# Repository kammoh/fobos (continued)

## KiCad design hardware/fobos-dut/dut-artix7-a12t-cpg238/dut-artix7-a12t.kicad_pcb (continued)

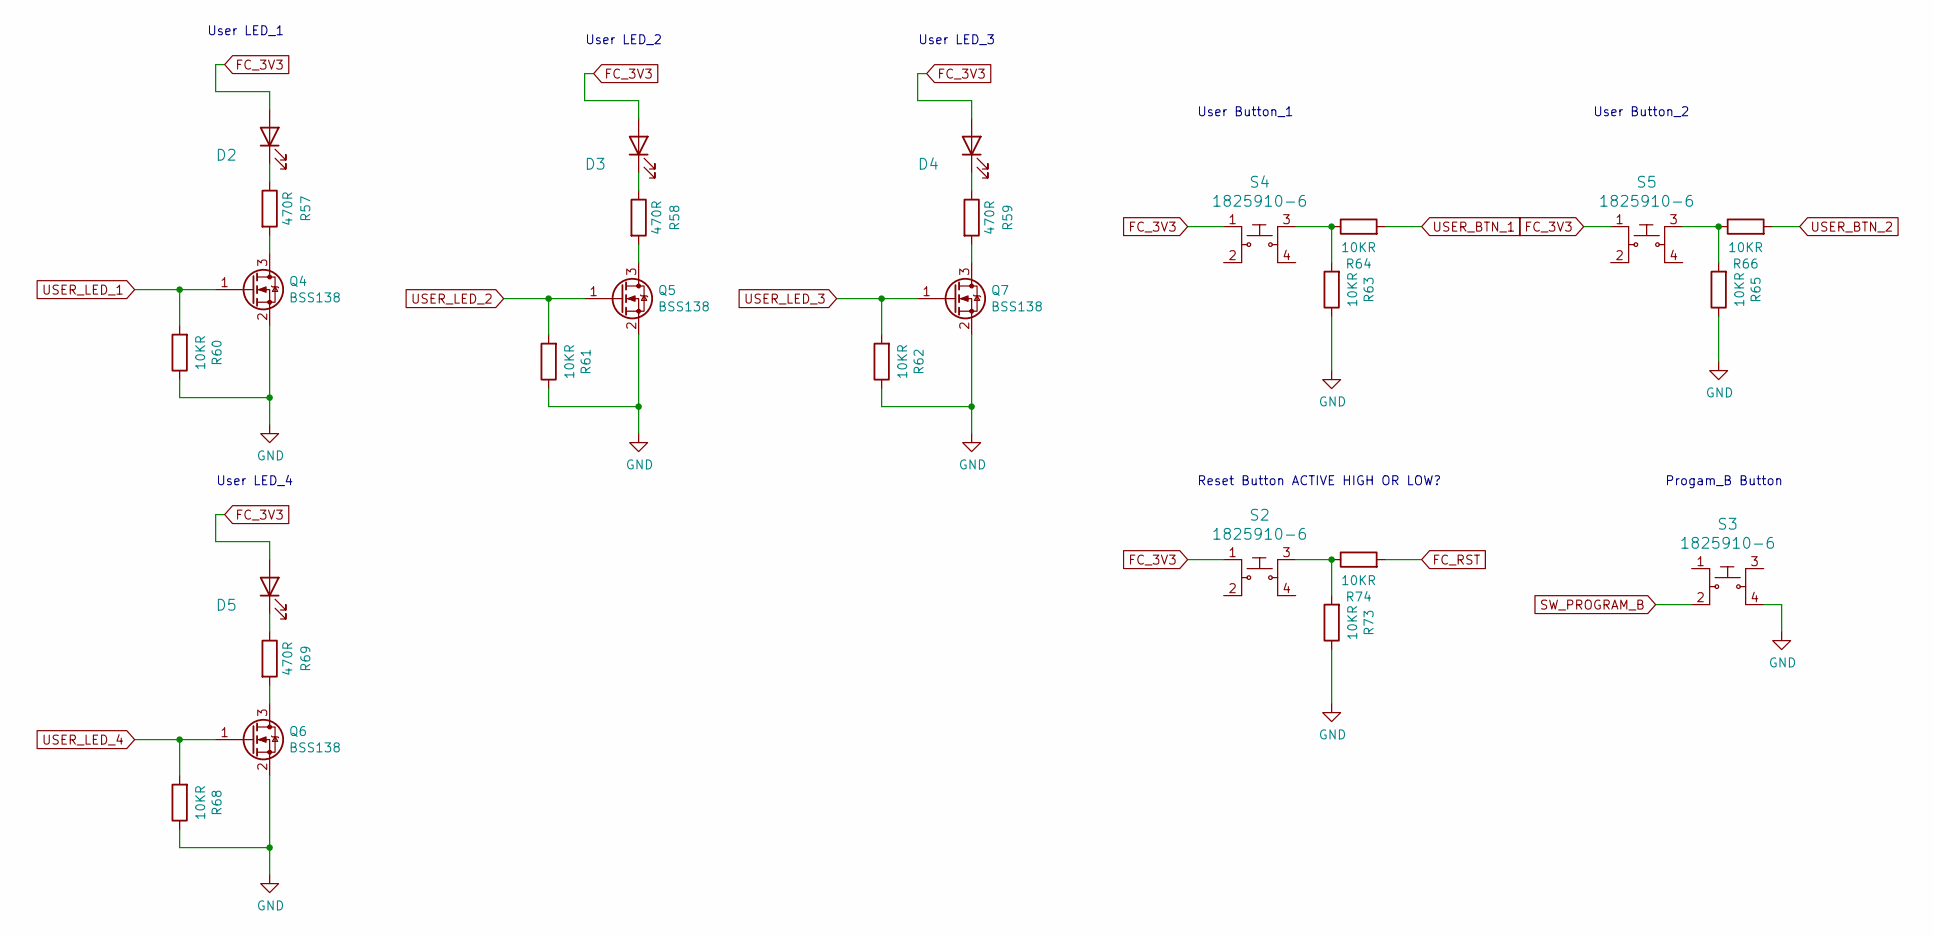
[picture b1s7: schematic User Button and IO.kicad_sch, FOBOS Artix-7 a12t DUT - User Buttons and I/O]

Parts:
D2, D3, D4, D5: LG_L29K-G2J1-24-Z; LED_0603_1608Metric; MPN LG L29K-G2J1-24-Z; Digi-Key_PN 475-2709-1-ND
Q4, Q5, Q6, Q7: BSS138; SOT-23; MPN BSS138
R57, R58, R59, R69: 470R; R_0603_1608Metric; MPN ERJ-U03J471V
R60, R61, R62, R63, R64, R65, R66, R68, R73, R74: 10KR; R_0603_1608Metric; MPN ERJ-3EKF1002V
S2, S3, S4, S5: 1825910-6; Switch_Tactile_THT_6x6mm; MPN 1825910-6; Digi-Key_PN 450-1650-ND

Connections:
FC_RST: R74.2; also elsewhere on the board
GND: Q4.2 (S), Q5.2 (S), Q6.2 (S), Q7.2 (S), R60.1, R61.1, R62.1, R63.1, R65.1, R68.1, R73.1, S3.4; also elsewhere on the board
unnamed: D2.1 (K), R57.1
unnamed: D3.1 (K), R58.1
unnamed: D4.1 (K), R59.1
unnamed: D5.1 (K), R69.1
unnamed: Q4.3 (D), R57.2
unnamed: Q5.3 (D), R58.2
unnamed: Q6.3 (D), R69.2
unnamed: Q7.3 (D), R59.2
unnamed: R63.2, R64.1, S4.3
unnamed: R65.2, R66.1, S5.3
unnamed: R73.2, R74.1, S2.3
SW_PROGRAM_B: S3.2; also elsewhere on the board
USER_BTN_1: R64.2; also elsewhere on the board
USER_BTN_2: R66.2; also elsewhere on the board
USER_LED_1: Q4.1 (G), R60.2; also elsewhere on the board
USER_LED_2: Q5.1 (G), R61.2; also elsewhere on the board
USER_LED_3: Q7.1 (G), R62.2; also elsewhere on the board
USER_LED_4: Q6.1 (G), R68.2; also elsewhere on the board

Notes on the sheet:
User LED_2
User LED_3
User LED_1
Reset Button ACTIVE HIGH OR LOW?
User Button_1
User LED_4
Progam_B Button
User Button_2

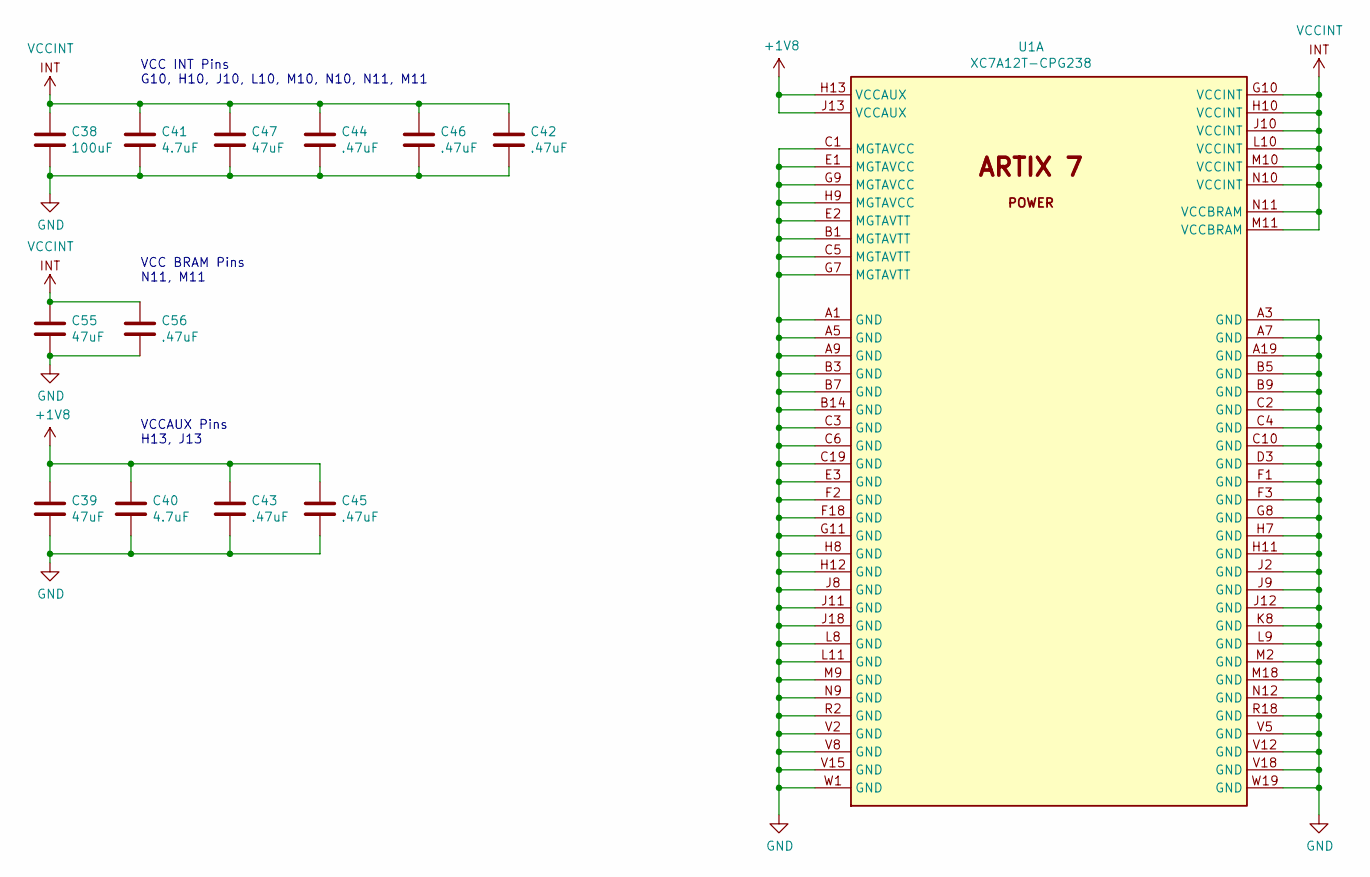
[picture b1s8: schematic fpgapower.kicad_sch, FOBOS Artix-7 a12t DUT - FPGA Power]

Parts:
C38: 100uF; C_1210_3225Metric_Pad1.33x2.70mm_HandSolder; MPN JMK325ABJ107MM-P
C39, C47, C55: 47uF; C_0603_1608Metric_Pad1.08x0.95mm_HandSolder; MPN 06036D476MAT2A
C40, C41: 4.7uF; C_0402_1005Metric_Pad0.74x0.62mm_HandSolder; MPN GRM155R60J475ME87J
C42, C43, C44, C45, C46, C56: .47uF; C_0402_1005Metric_Pad0.74x0.62mm_HandSolder; MPN C0402C474K9PACTU
U1: XC7A12T-CPG238; Xilinx_CPG238

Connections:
GND: C38.2, C39.2, C40.2, C41.2, C42.2, C43.2, C44.2, C45.2, C46.2, C47.2, C55.2, C56.2, U1.A1 (GND), U1.A3 (GND), U1.A5 (GND), U1.A7 (GND), U1.A9 (GND), U1.A19 (GND), U1.B1 (MGTAVTT), U1.B3 (GND), U1.B5 (GND), U1.B7 (GND), U1.B9 (GND), U1.B14 (GND), U1.C1 (MGTAVCC), U1.C2 (GND), U1.C3 (GND), U1.C4 (GND), U1.C5 (MGTAVTT), U1.C6 (GND), U1.C10 (GND), U1.C19 (GND), U1.D3 (GND), U1.E1 (MGTAVCC), U1.E2 (MGTAVTT), U1.E3 (GND), U1.F1 (GND), U1.F2 (GND), U1.F3 (GND), U1.F18 (GND), U1.G7 (MGTAVTT), U1.G8 (GND), U1.G9 (MGTAVCC), U1.G11 (GND), U1.H7 (GND), U1.H8 (GND), U1.H9 (MGTAVCC), U1.H11 (GND), U1.H12 (GND), U1.J2 (GND), U1.J8 (GND), U1.J9 (GND), U1.J11 (GND), U1.J12 (GND), U1.J18 (GND), U1.K8 (GND), U1.L8 (GND), U1.L9 (GND), U1.L11 (GND), U1.M2 (GND), U1.M9 (GND), U1.M18 (GND), U1.N9 (GND), U1.N12 (GND), U1.R2 (GND), U1.R18 (GND), U1.V2 (GND), U1.V5 (GND), U1.V8 (GND), U1.V12 (GND), U1.V15 (GND), U1.V18 (GND), U1.W1 (GND), U1.W19 (GND); also elsewhere on the board
VCCINT: C38.1, C41.1, C42.1, C44.1, C46.1, C47.1, C55.1, C56.1, U1.G10 (VCCINT), U1.H10 (VCCINT), U1.J10 (VCCINT), U1.L10 (VCCINT), U1.M10 (VCCINT), U1.M11 (VCCBRAM), U1.N10 (VCCINT), U1.N11 (VCCBRAM); also elsewhere on the board

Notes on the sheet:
VCCAUX Pins H13, J13
VCC BRAM Pins N11, M11
VCC INT Pins G10, H10, J10, L10, M10, N10, N11, M11

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
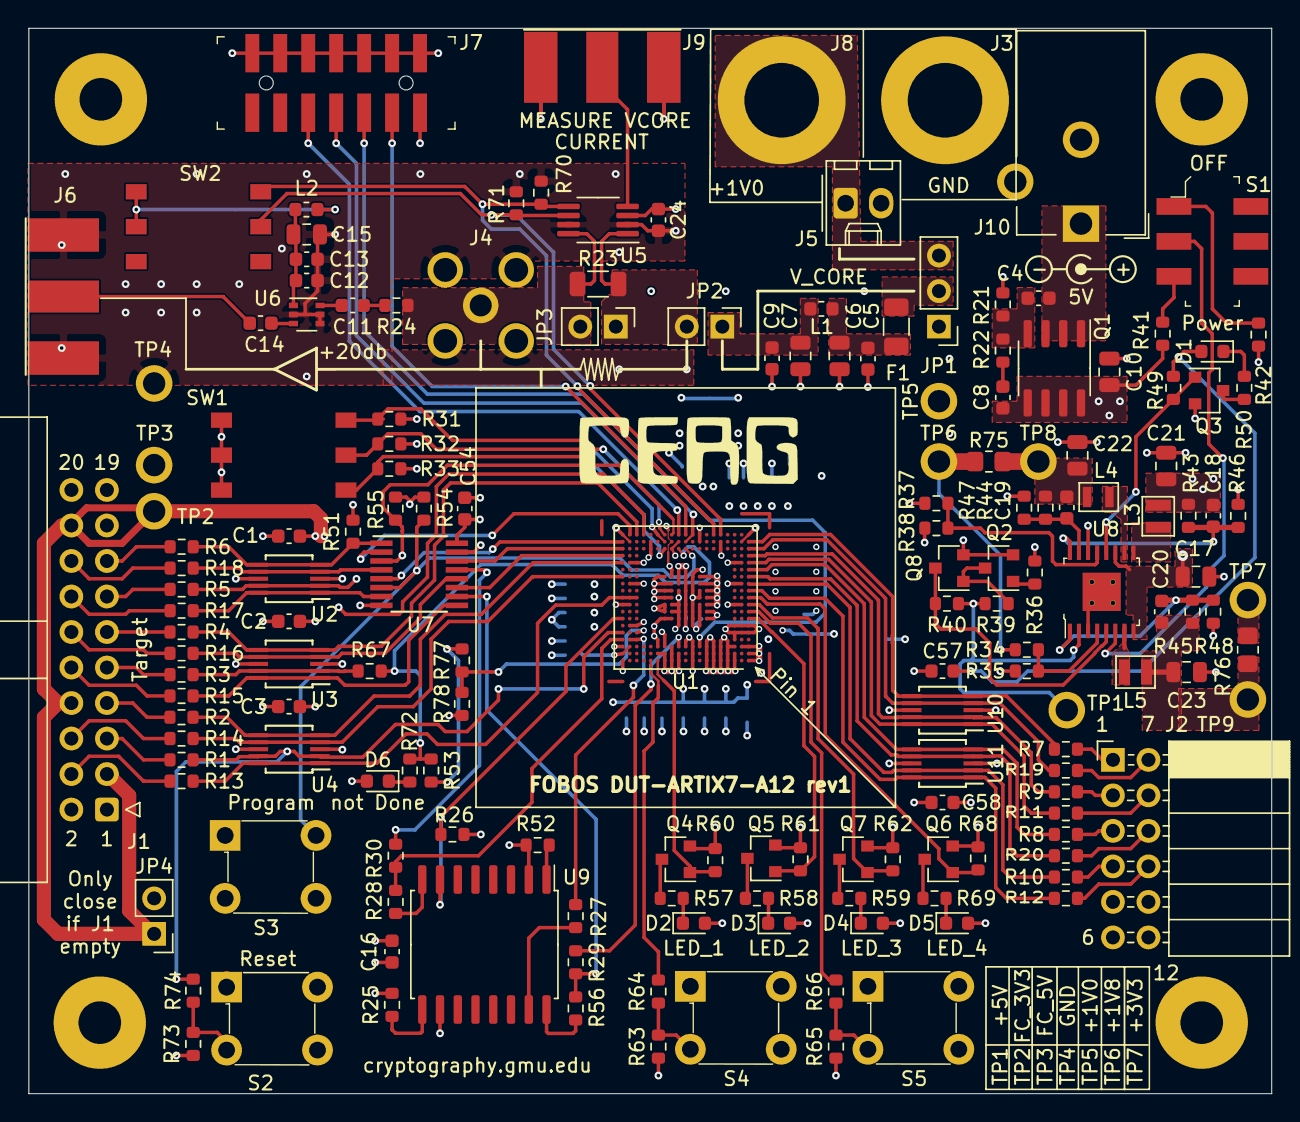
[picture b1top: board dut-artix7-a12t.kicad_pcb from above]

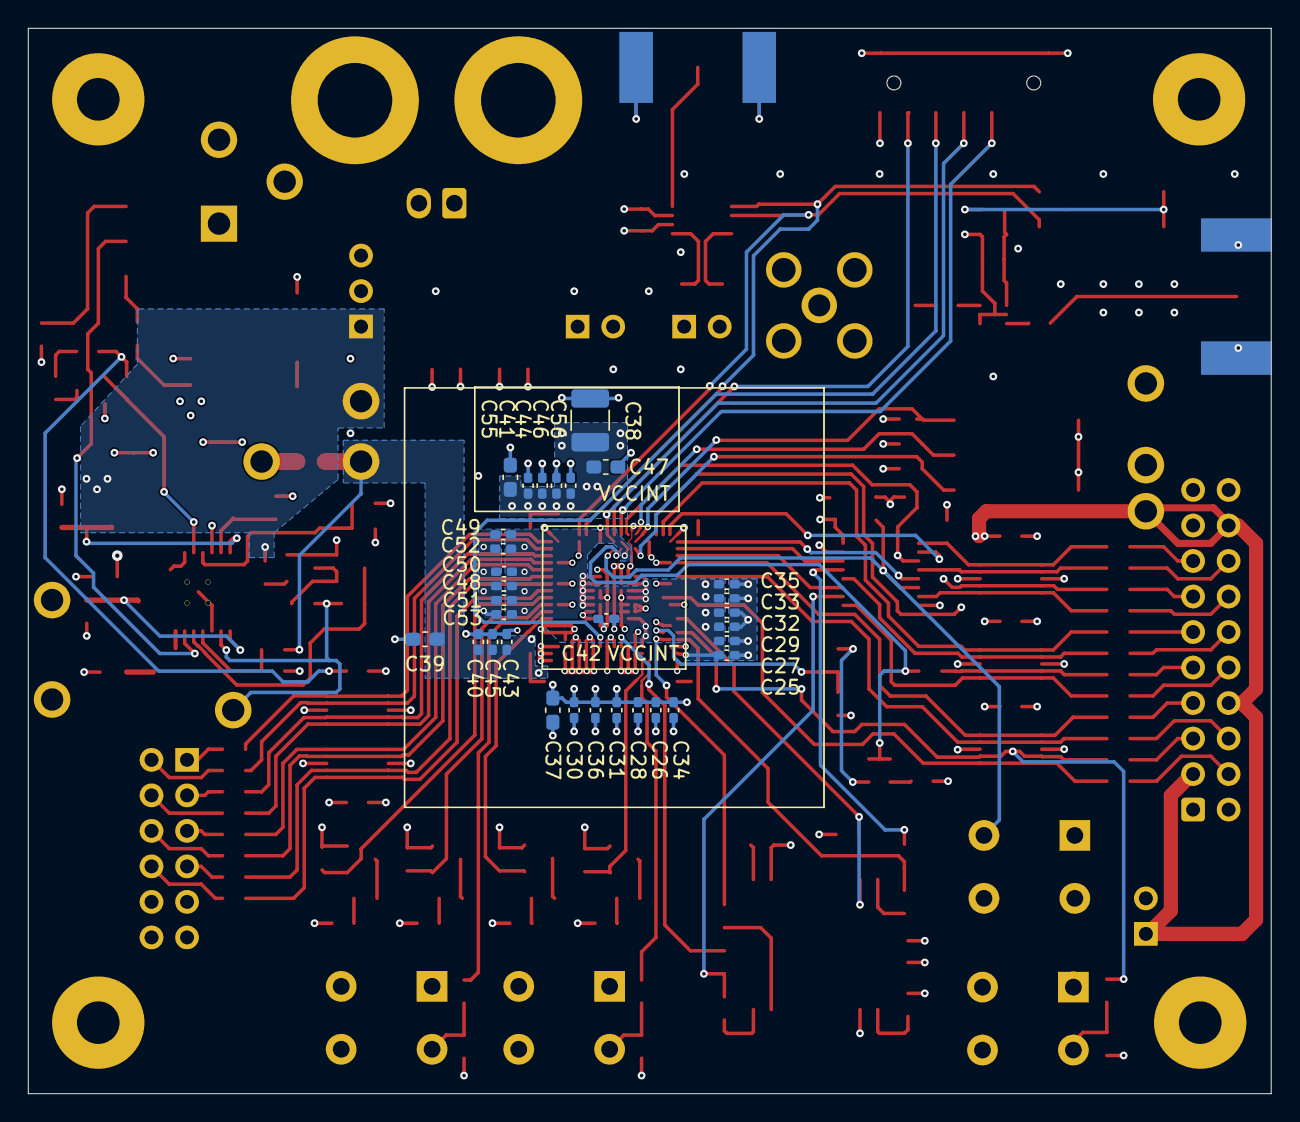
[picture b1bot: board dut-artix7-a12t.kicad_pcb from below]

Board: 4 copper layers, 88.9 x 76.2 mm, 201 parts (31 on the bottom side), 126 nets.

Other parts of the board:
TP6, TP7, TP8, TP9: 5281

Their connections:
/Power/pre3V3: TP9.1; also elsewhere on the board

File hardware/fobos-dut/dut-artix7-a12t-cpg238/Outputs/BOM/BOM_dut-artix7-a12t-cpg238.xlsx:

Artix-7 DUT
Ref# | Qty. | Value | Size | Mouser # | Mfr. # | Manufacturer | Description
R29 R30 R37 R67 | 4 | 0R | 0603 | 603-RC0603JR-070RL | RC0603JR-070RL | Yageo | Thick Film Resistors - SMD 0 Ohms 100 mW 0603 5%
R23 | 1 | 0R1 | 1206 | 71-WSL1206R1000DEA | WSL1206R1000DEA | Vishay | Current Sense Resistors - SMD 1/4watt .1ohms .5%
R24 | 1 | 49R9 | 0603
R75 R76 | 2 | 0R1 | 0805
R22 | 1 | 100R | 0603 | 603-RC0603FR-13100RL | RC0603FR-13100RL | Yageo | Thick Film Resistors - SMD 100 OHM 1%
R36 R77 R78 | 3 | 1k | 0603 | 603-RC0603FR-071KL | RC0603FR-071KL | Yageo | Thick Film Resistors - SMD 1K OHM 1%
R35 R42 R43 R44 R45 R51 R60 R61 R62 R63 R64 R65 R66 R68 R70 R71 R73 R74 | 18 | 10k | 0603 | 603-RC0603FR-0710KL | RC0603FR-0710KL | Yageo | Thick Film Resistors - SMD 10K OHM 1%
R38 R39 R40 R49 | 4 | 100k | 0603 | 652-CR0603-FX-103ELF | CR0603-FX-1003ELF | Bourns | Thick Film Resistors - SMD 100K 1% 1/10 WATT
R21 | 1 | 1M | 0603 | 652-CR0603FX-1004ELF | CR0603-FX-1004ELF | Bourns | Thick Film Resistors - SMD 1M 1% 1/10W
R46 R47 | 2 | 120k | 0603 | 603-RC0603FR-13120KL | RC0603FR-13120KL | Yageo | Thick Film Resistors - SMD 120 kOhms 100-200 mW 0603 1%
R7 R8 R9 R10 R11 R12 R19 R20 R53 R72 | 10 | 200R | 0603 | 603-RC0603FR-07200RL | RC0603FR-07200RL | Yageo | Thick Film Resistors - SMD 200 OHM 1%
R1 R2 R3 R4 R5 R6 R13 R14 R15 R16 R17 R18 | 12 | 22R | 0603 | 603-RC0603FR-0722RL | RC0603FR-0722RL | Yageo | Thick Film Resistors - SMD 22 OHM 1%
R27 R28 R56 | 3 | 33R, 0.5% | 0603 | 667-ERA-3AHD330V | ERA-3AHD330V | Panasonic | Thin Film Resistors - SMD 0603 33ohms 50ppm 0.5% AEC-Q200
R34 | 1 | 3k48 | 0603 | 603-RC0603FR-073K48L | RC0603FR-073K48L | Yageo | Thick Film Resistors - SMD 3.48 kOhms 100mW 0603 1%
R57 R58 R59 R69 | 4 | 470R | 0603 | 603-RC0603FR-10470RL | RC0603FR-10470RL | Yageo | Thick Film Resistors - SMD 470 OHM 1%
R25 R26 R31 R32 R33 R41 R52 R54 R55 | 9 | 4k7 | 0603 | 603-RC0603FR-134K7L | RC0603FR-134K7L | Yageo | Thick Film Resistors - SMD 4.7 kOhms 100-200mW 0603 1%
R48 | 1 | 57k6 | 0603 | 652-CR0603FX-5762ELF | CR0603-FX-5762ELF | Bourns | Thick Film Resistors - SMD 57.6K ohm 1%
R50 | 1 | 800R | 0603 | 603-RC0603FR-07806RL | RC0603FR-07806RL | Yageo | Thick Film Resistors - SMD 806 Ohms 100 mW 0603 1%
C8 | 1 | 10nF | 0603 | 603-CS0603KRX79BB103 | CS0603KRX7R9BB103 | Yageo | Multilayer Ceramic Capacitors MLCC - SMD/SMT 10 nF 50 V 10% Ceramic Capacitors
C1 C2 C3 C4 C5 C9 C11 C13 C14 C16 C24 C54 C57 C58 | 14 | 100nF | 0603 | 77-VJ0603Y104JXQPBC | VJ0603Y104JXQPW1BC | Vishay / Vitramon | Multilayer Ceramic Capacitors MLCC - SMD/SMT 0603 0.1uF 10volts X7R 5%
C6 C10 C22 C23 | 4 | 10uF | 0805 | 81-GRM21BC81C106MA3L | GRM21BC81C106MA73L | Murata Electronics | Multilayer Ceramic Capacitors MLCC - SMD/SMT 0805 10uF 16volts X6S 20%
C18 C19 C20 | 3 | 20pF | 0603 | 80-C0603C200K8HACTU | C0603C200K8HACTU | KEMET | Multilayer Ceramic Capacitors MLCC - SMD/SMT 10V 20pF X8R 0603 10%
C15 | 1 | 2u2F | 0805
C17 C21 | 2 | 22uF | 0805 | 187-CL21A226KQCLRNC | CL21A226KQCLRNC | Samsung | Multilayer Ceramic Capacitors MLCC - SMD/SMT 22uF+/-10% 6.3V X5R 2012
C12 | 1 | 4n7F | 0603 | 710-885012206087 | 885012206087 | Wurth Electronics | Multilayer Ceramic Capacitors MLCC - SMD/SMT WCAP-CSGP 4700pF 0603 10% 50V MLCC
C29 C30 C31 C32 C33 C34 C35 C36 C42 C43 C44 C45 C46 C50 C51 C52 C53 C56 | 18 | 470nF | 0402 | 963-JMK105BJ474KV-F | JMK105BJ474KV-F | Taiyo Yuden | CAP CER 0.47UF 6.3V X5R 0402
C25 C26 C27 C28 C40 C41 C48 C49 | 8 | 4.7uF | 0402 | 81-GRM155R60J475ME8J | GRM155R60J475ME87J | Murata Electronics | CAP CER 4.7UF 6.3V X5R 0402
C37 C39 C47 C55 | 4 | 47uF | 0603 | 81-GRM21BR60J476ME5K | GRM21BR60J476ME15K | Murata Electronics | Multilayer Ceramic Capacitors MLCC - SMD/SMT 0805 47uF 6.3volts
C7 | 1 | 47uF | 0805
C38 | 1 | 100uF | 1210
L1 L2 | 2 | 1k/500mA | 0603 | 963-FBMH1608HM102-T | FBMH1608HM102-T | Taiyo Yuden | Ferrite Beads HI CUR CHIP BD 0603 1000OHMS 25%
L3 | 1 | 1.5uH |  | 652-SRN2012-1R5M | SRN2012-1R5M | Bourns Inc. | FIXED IND 1.5UH 1.8A 108MOHM SMD
L4 | 1 | 3.3uH |  | 963-BRC2012T3R3MD | BRC2012T3R3MD | Taiyo Yuden | FIXED IND 3.3UH 870MA 221MOHM SM
L5 | 1 | 2.2uH |  | 652-SRN2010-2R2M | SRN2010-2R2M | Bourns Inc. | FIXED IND 2.2UH 1.7A 170MOHM SMD
D1 D2 D3 D4 D5 D6 | 6 | green | 0603 | 604-APT1608CGCK | APT1608CGCK | Kingbright | Standard LEDs - SMD Green Water Clear 570nm 40mcd 120deg
Q3 Q4 Q5 Q6 Q7 | 5 | BSS138L | SOT-23-3 | 512-BSS138L | BSS138L | ON Semiconductor | MOSFET 0.20A, 50V N-Channel SOT-23 MOSFET
Q1 | 1 | FDS9435A | SOIC-8 | 512-FDS9435A | FDS9435A | ON Semiconductor/Fairchild | MOSFET SO-8 SGL P-CH -30V
Q2 Q8 | 2 | 3904 | SOT-23-3 | 863-MMBT3904LT1G | MMBT3904LT1G | ON Semiconductor | Bipolar Transistors - BJT NPN GENERAL PURPOSE
U8 | 1 | LTC3569EFE#PBF | 16TSSOP | LTC3569EFE#PBF | LTC3569EFE#PBF | Analog Devices Inc. | Switching Voltage Regulators Programmable 1.2A and 2X600mA, Triple Buck Regulat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
U5 | 1 | INA225 | MSOP-8 | 595-INA225AIDGKT | INA225AIDGKT | Texas Instruments | Current Sense Amplifiers 36V Bidir 0-Drift Ser Crnt-Shunt Mon
U7 | 1 | TS3A5018DBQR | 16SSOP | 595-TS3A5018DBQR | TS3A5018DBQR | Texas Instruments | Analog Switch ICs 10-Ohm Quad SPDT Analog Switch
U9 | 1 | IS25LP256D-JMLE | 16SOIC | IS25LP256D-JMLE | IS25LP256D-JMLE | ISSI, Integrated Silicon Solution Inc | NOR Flash 256M 3V 166MHZ Serial Flash
U6 | 1 | BGA2801 | SOT-363 | 771-BGA2801115 | BGA2801,115 | NXP USA Inc. | RF Amplifier 6CH MMIC Amp 3.8 dB 3.3V 14.3mA 2.8GHz
U1 | 1 | XC7A12T-cpg238 | CPG238 | 217-XC7A12T-1CPG238C | XC7A12T-1CPG238C | Xilinx | FPGA - Field Programmable Gate Array XC7A12T-1CPG238C
F1 | 1 | MF-MSMF050-2 | 1206 | 667-ERB-RG2R00V | ERB-RG2R00V | Panasonic Electronic Components | FUSE BOARD MOUNT 2A 63VDC 1206
U2 U3 U4 U10 U11 | 5 | Fuse | MSOP-10 | 576-SP3003-04ATG | SP3003-04ATG | Littelfuse | ESD Suppressors / TVS Diodes 4 Ch 8kV 0.65pF SPA
J10 | 1 | Barrel Jack |  | 490-PJ-102AH | PJ-102AH | CUI | DC Power Connectors Power Jacks
J4 | 1 | SMA Edge |  | 530-142-0701-801 | 142-0701-801 | Johnson / Cinch Connectivity Solutions | RF Connectors / Coaxial Connectors PC END MT JCK GLD .062" BOARD THICK
J6 J9 | 2 | SMA Vertical |  | 712-CONSMA008-G | CONSMA008-G | Linx Technologies | RF Connectors / Coaxial Connectors SMA Female PCB Mnt, Extended, Gold
J1 | 1 | Shrd Hdr | 2x10 | 517-30320-5002 | 30320-5002HB | 3M Electronic Solutions Division | Headers & Wire Housings 20P R/A 4WALL GLDFL
JP1, JP2, JP3, JP4 | 1 | Pin Header | 1x36 | 649-68001-236HLF | 68001-236HLF | Amphenol FCI | Headers & Wire Housings 36P HDR
J5 | 1 | Molex | 1x2-P2.54mm | 538-22-11-2022 | 22-11-2022 | Molex | Connector_Molex:Molex_KK-254_AE-6410-02A_1x02_P2.54mm_Vertical, gold
J7 | 1 | Shrd Hdr | 2x7 2mm | 538-87832-1420 | 878321420 | Molex | Headers & Wire Housings 14P SMD PB FREE SHRD
J3 J8 | 2 | 575-8 |  | 534-575-8 | 575-8 | Keystone Electronics | CONN BANANA JACK SOLDER
J2 | 1 | Pin Socket | 2x6 90 deg | 200-SSW10602FDRA | SSW-106-02-F-D-RA | Samtec | Board to Board & Mezzanine Connectors Tiger Buy Socket Strip with PCB Tails, 0.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
TP1 TP2 TP3 TP4 TP5 TP6 TP7 TP8 TP9 | 9 | 5281 |  | 534-5281 | 5281 | Keystone Electronics | Circuit Board Hardware - PCB TEST POINT BLACK MULTIPURPOSE
S1 | 1 | JS202011SCQN |  | 611-JS202011SCQN | JS202011SCQN | C&K | SWITCH SLIDE DPDT 300MA 6V
S2 S3 S4 S5 | 4 | 1825910-6 |  |  | 1825910-6 | TE Connectivity ALCOSWITCH Switches | SWITCH TACTILE SPST-NO 0.05A 24V
SW1 SW2 | 2 | SW_DIP_x03 |  | 490-DS04254203BK-SMT | DS04-254-2-03BK-SMT | CUI Devices | DIP SWITCH, SPST, 2.54 PITCH, FL

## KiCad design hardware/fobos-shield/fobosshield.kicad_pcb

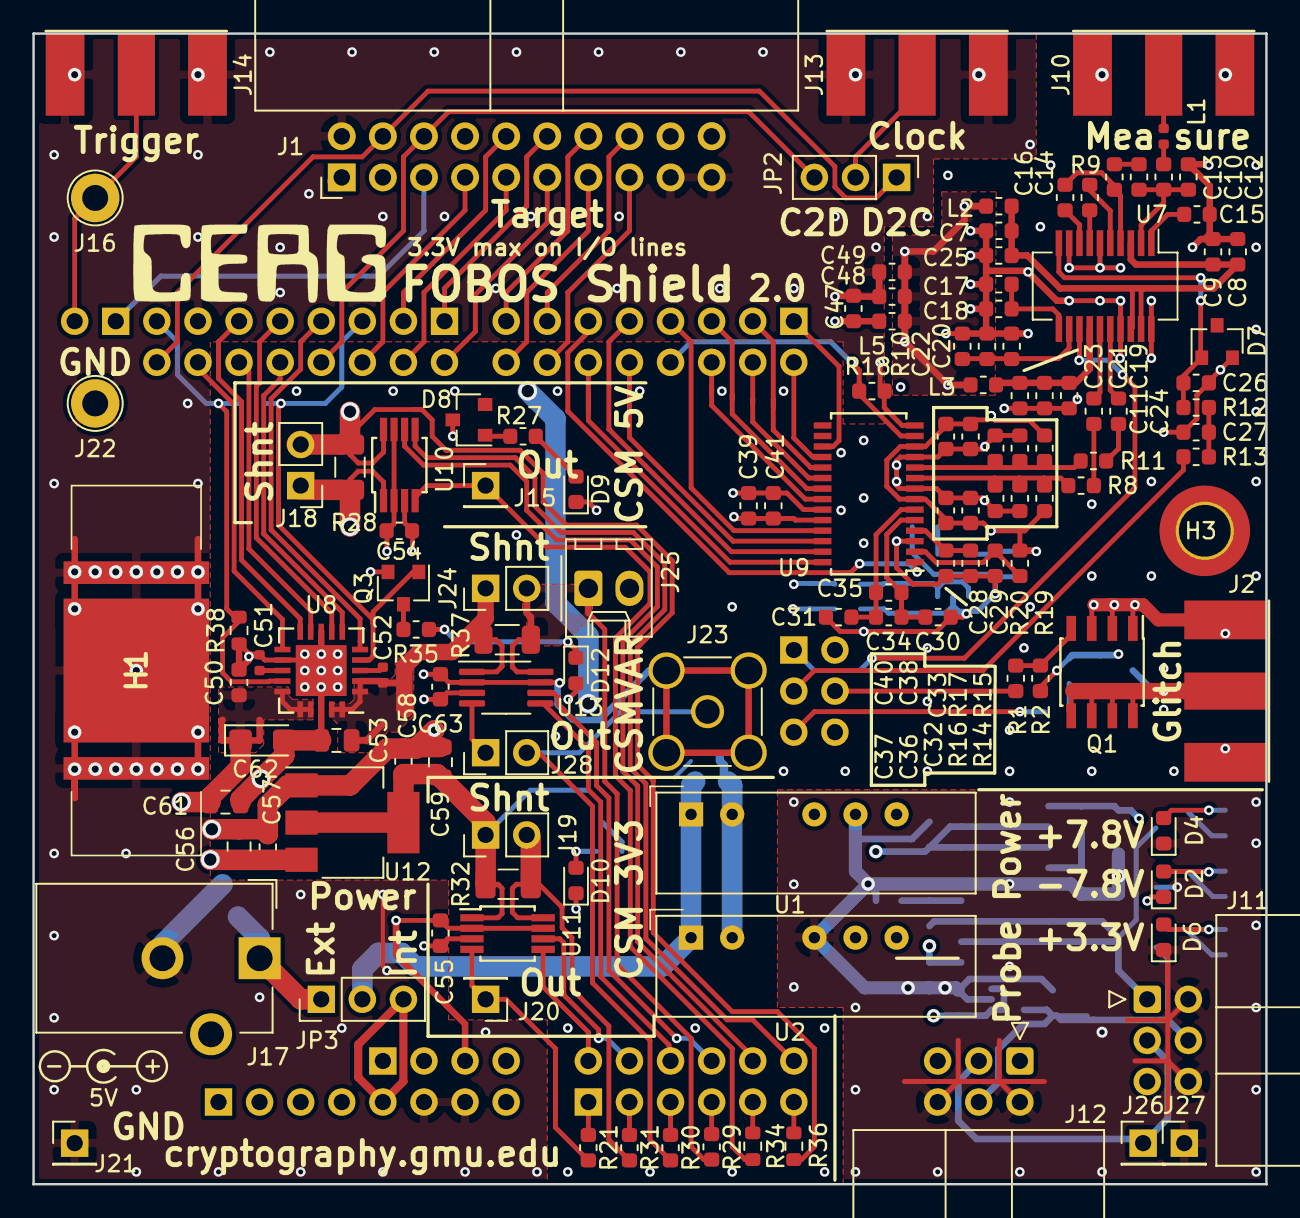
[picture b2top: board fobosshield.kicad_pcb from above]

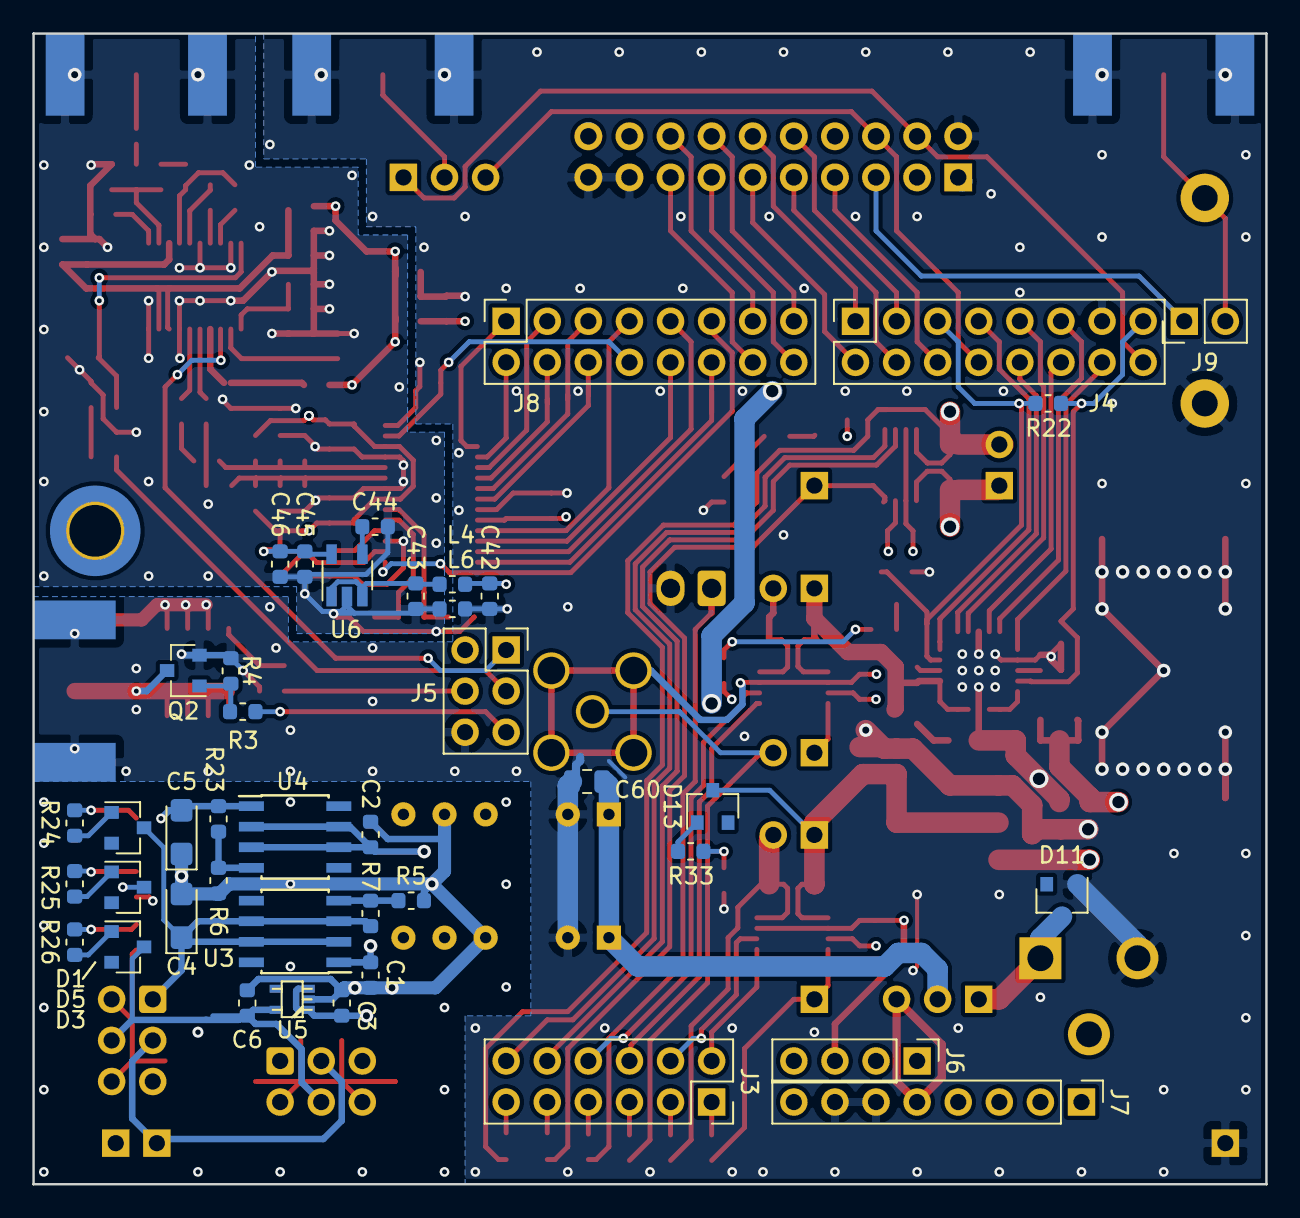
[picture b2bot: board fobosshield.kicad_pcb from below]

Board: 4 copper layers, 76.2 x 71.1 mm, 168 parts (42 on the bottom side), 122 nets.

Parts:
C1, C2: 100n, 16V; C_0603_1608Metric
C3, C6, C7, C23, C26, C27, C43, C45, C50: 1uF; C_0603_1608Metric
C4, C5, C62: 1uF; CP_EIA-3216-18_Kemet-A
C8, C10, C11, C14, C15, C16, C18, C21, C22, C24, C25, C28, C30, C31, C34, C36, C38, C39, C42, C46, C48, C54, C55, C57, C58, C63: 100n; C_0603_1608Metric
C9, C17, C19, C20: 1nF; C_0603_1608Metric
C12: 22pF; C_0603_1608Metric
C13: 18nF; C_0603_1608Metric
C29, C35: 10u; C_0603_1608Metric
C32, C33: 100p; C_0603_1608Metric
C37, C40, C41, C44, C47: 10n; C_0603_1608Metric
C49: 2u2; C_0603_1608Metric
C51: 10n; C_0402_1005Metric
C52: 220p; C_0402_1005Metric
C53, C56, C59: 10uF; C_0805_2012Metric
C60, C61: 10uF, 10V; C_0805_2012Metric
D1: 6V2; D_SOT-23_ANK
D2, D4, D6, D9, D10, D12: green; LED_0603_1608Metric
D3, D13: 2V4; D_SOT-23_ANK
D5, D11: 5V1; D_SOT-23_ANK
D7: BAV99; SOT-23
D8: 3V9; D_SOT-23_ANK
H1: 573100D00010G
H3: MountingHole; MountingHole_3.2mm_M3_DIN965_Pad_TopBottom
J1: Target; IDC-Header_2x10_P2.54mm_Horizontal
J2: Glitch; SMA-JOHNSON-142-0701-801
J3: Analog; PinHeader_2x06_P2.54mm_Vertical_flipped
J4: IOH; PinHeader_2x08_P2.54mm_Vertical_Flipped
J5: SPI; PinSocket_2x03_P2.54mm_Vertical
J6: Analog2; PinHeader_1x04_P2.54mm_Vertical
J7: Power; PinHeader_1x08_P2.54mm_Vertical
J8: IOL; PinHeader_2x08_P2.54mm_Vertical_Flipped
J9: SPI2; PinHeader_1x02_P2.54mm_Vertical
J10: ADCin; SMA-JOHNSON-142-0701-801
J11: PP1; IDC-Header_2x03_P2.54mm_Horizontal
J12: PP2; IDC-Header_2x03_P2.54mm_Horizontal
J13: Clock; SMA-JOHNSON-142-0701-801
J14: Trigger; SMA-JOHNSON-142-0701-801
J15: CSM5VCur; PinHeader_1x01_P2.54mm_Vertical
J16: Conn_01x01; TestPoint_Loop_D2.60mm_Drill1.6mm_Beaded
J17: Barrel_Jack_Switch; BarrelJack_CUI_PJ-102AH_Horizontal
J18, J19, J24: Conn_01x02; PinHeader_1x02_P2.54mm_Vertical
J20: CSM3V3Cur; PinHeader_1x01_P2.54mm_Vertical
J21: GND; PinHeader_1x01_P2.54mm_Vertical
J22: GND; TestPoint_Loop_D2.60mm_Drill1.6mm_Beaded
J23: Conn_Coaxial_Power; SMA_Amphenol_901-144_Vertical
J25: V_Var; Molex_KK-254_AE-6410-02A_1x02_P2.54mm_Vertical
J26: AUX; PinHeader_1x01_P2.54mm_Vertical
J27: GNDP; PinHeader_1x01_P2.54mm_Vertical
J28: CSM5VCur; PinHeader_1x02_P2.54mm_Vertical
JP2: ExtClkSel; PinHeader_1x03_P2.54mm_Vertical
JP3: Power Ext or int; PinHeader_1x03_P2.54mm_Vertical
L1: 120nH; L_0402_1005Metric
L2, L3, L4, L5, L6: 1k/500mA; L_0603_1608Metric
Q1: IRF7807Z; SOIC-8_3.9x4.9mm_P1.27mm
Q2: IRLML2502; SOT-23
Q3: BSS138L; SOT-23
R1, R3: 1R; R_0603_1608Metric
R2, R4, R10, R38: 10k; R_0603_1608Metric
R5, R6: 1K2, 1%; R_0603_1608Metric
R7, R23: 240R, 1%; R_0603_1608Metric
R8, R11: 33R, 0.5%; R_0603_1608Metric
R9: 274R; R_0603_1608Metric
R12, R13, R19: 2k; R_0603_1608Metric
R14, R15, R16, R17, R20: 1k; R_0603_1608Metric
R18, R24, R25, R26, R33: 100R; R_0603_1608Metric
R21, R29, R30, R31, R34, R36: 1k69 1%; R_0603_1608Metric
R22: 22K; R_0603_1608Metric
R27: 330R; R_0603_1608Metric
R28, R32, R37: 0R1; R_1206_3216Metric
R35: 470R; R_0603_1608Metric
U1: RB-0509D; Converter_DCDC_muRata_NMAxxxxSC_THT
U2: REE-0505S; Converter_DCDC_muRata_NMAxxxxSC_THT
U3: LM317L_SO8; SOIC-8_3.9x4.9mm_P1.27mm
U4: LM337L_SO8; SOIC-8_3.9x4.9mm_P1.27mm
U5: LD59015; sot323-5
U6: LP3985IM5-3.0; TSOT-23-5
U7: AD8331; QSOP-20_3.9x8.7mm_P0.635mm
U8: TPS7A7100_VQFN20; Texas_VQFN-RGW-20
U9: AD9215; TSSOP-28_4.4x9.7mm_P0.65mm
U10, U11, U13: INA225; MSOP-8_3x3mm_P0.65mm
U12: LD1117S33TR_SOT223; SOT-223-3_TabPin2

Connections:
5Vclean: C48.2, C49.2, L2.2, L3.2, L5.1
/Ardu/A0: J3.1, R21.1
/Ardu/A1: J3.3, R31.1
/Ardu/A2: J3.5, R30.1
/Ardu/A3: J3.7, R29.1
/Ardu/A4: J3.9, R34.1
/Ardu/A5: J3.11, R36.1
/Power/3V3P: C6.1, D3.1, J11.4, J12.4, U5.5
/Power/+7V8P: C4.1, D1.1, J11.1, J12.1, R7.1, U3.2, U3.3, U3.6, U3.7
/Power/-7V8P: C5.2, D2.1, J11.5, J12.5, R23.1, U4.1
/Power/GNDP: C1.2, C2.1, C3.2, C4.2, C5.1, C6.2, D4.1, D5.1, D6.1, J11.2, J11.6, J12.2, J12.6, J27.1, R5.2, R6.2, U1.5, U2.4, U5.2
ADC_CLK: J8.8, R18.2, U9.13
ADC_D0: J8.1, U9.17
ADC_D1: J8.2, U9.18
ADC_D2: J8.3, U9.19
ADC_D3: J8.4, U9.20
ADC_D4: J8.5, U9.21
ADC_D5: J8.6, U9.22
ADC_D6: J8.7, U9.25
ADC_D7: J8.10, U9.26
ADC_D8: J8.9, U9.27
ADC_D9: J8.12, U9.28
ADC_OR: J8.11, U9.1
CSM3V3Cur: J20.1, R21.2, U11.4
CSM3V3Gain0: J3.2, U11.5
CSM3V3Gain1: J3.4, U11.6
CSM5VCur: J15.1, R34.2, U10.4
CSM5VGain0: J3.12, U10.5
CSM5VGain1: J3.10, U10.6
CSMVarCur: J23.1, J28.2, R30.2
CSMVarGain0: J3.6, U13.5
CSMVarGain1: J3.8, U13.6
FC2D_CLK: J1.6, J4.8, JP2.3
FC2D_HS: J1.11, J4.2
FC_3V3: J1.3, J1.18, J19.2, R31.2, R32.2, U11.8
FC_5V: J1.1, J1.20, J18.2, R28.2, R36.2, U10.8
FC_DIO0: J1.10, J4.3
FC_DIO1: J1.12, J4.1
FC_DIO2: J1.14, J8.15
FC_DIO3: J1.16, J8.13
FC_IO: J1.7, J4.6
FC_PROG: J1.15, J8.14
FC_RST: J1.5, J9.1
FC_Var: J24.2, J25.1, R29.2, R37.2, U13.8
FD2C_CLK: J1.4, J4.16, JP2.1
FD2C_HS: J1.13, J8.16
FD_TF: J1.9, J4.4
GND: C39.1, C41.1, C42.1, C47.1, C48.1, C49.1, C50.2, C51.2, C53.2, C56.2, C57.2, C58.2, C59.2, C60.2, C61.2, C62.2, D9.1, D10.1, D11.2, H1.1, H1.2, H1.3, J1.2, J1.17, J1.19, J2.2, J4.13, J5.6, J7.6, J7.7, J13.2, J14.2, J17.2, J21.1, J22.1, J25.2, L6.2, Q1.1, Q1.2, Q1.3, Q2.2, Q3.2, R2.2, R4.2, R18.1, R38.1, U1.2, U2.2, U8.8, U8.12, U8.18, U8.21, U9.14, U9.23, U12.1
GNDA: C7.1, C8.1, C9.1, C12.1, C15.1, C17.1, C18.1, C19.1, C20.1, C21.1, C22.1, C23.1, C25.1, C26.1, C27.1, C28.1, C29.1, C30.2, C31.2, C32.2, C33.1, C36.1, C37.1, C38.1, C40.1, C43.1, C44.1, C45.1, C46.1, D7.2, J10.2, L6.1, R10.1, R16.2, R17.2, R20.1, U6.2, U7.6, U7.9, U7.17, U7.20, U9.3, U9.8, U9.11
Glitch: J5.4, R1.1
GlitchLP: J5.5, R3.1
IN: C50.1, C56.1, C57.1, C60.1, C61.1, C62.1, D8.1, J18.1, JP3.2, R28.1, U1.1, U2.1, U8.15, U8.16, U8.17, U10.1, U12.3
unnamed: C1.1, U1.6, U3.1
unnamed: C2.2, U1.4, U4.2, U4.3, U4.6, U4.7
unnamed: C3.1, U2.6, U5.1, U5.3
unnamed: C10.1, C12.2, C13.1, U7.2
unnamed: C10.2, L1.1
unnamed: C11.1, R8.1
unnamed: C11.2, U7.15
unnamed: C13.2, R9.2
unnamed: C14.1, U7.7
unnamed: C14.2, U7.5
unnamed: C15.2, U7.1
unnamed: C16.1, U7.8
unnamed: C16.2, R9.1, U7.4
unnamed: C17.2, C18.2, U7.11
unnamed: C19.2, C21.2, C23.2, L3.1, U7.14
unnamed: C20.2, C22.2, R10.2, U7.12
unnamed: C24.1, R11.1
unnamed: C24.2, U7.16
unnamed: C7.2, C8.2, C9.2, C25.2, L2.1, U7.3, U7.18, U7.19
unnamed: C26.2, D7.1, R12.1, U7.10
unnamed: C27.2, R12.2, R13.1
unnamed: C28.2, C29.2, U9.4
unnamed: C30.1, C34.2, C35.2, U9.5
unnamed: C31.1, C34.1, C35.1, U9.6
unnamed: C32.1, R8.2, R14.2, R16.1, U9.9
unnamed: C33.2, R11.2, R15.2, R17.1, U9.10
unnamed: C43.2, L4.1, U6.1, U6.3
unnamed: C44.2, U6.4
unnamed: C51.1, U8.13
unnamed: C52.1, C53.1, J24.1, R37.1, U8.1, U8.2, U8.19, U8.20, U13.1
unnamed: C52.2, U8.3
unnamed: C58.1, C59.1, D13.1, J19.1, R32.1, U11.1, U12.2
unnamed: D1.2, R24.2
unnamed: D2.2, R25.1
unnamed: D3.2, R26.1
unnamed: D4.2, R24.1
unnamed: D5.2, R25.2
unnamed: D6.2, R26.2
unnamed: D8.2, R27.1
unnamed: D9.2, R27.2
unnamed: D10.2, R33.2
unnamed: D11.1, J17.1, JP3.1
unnamed: D12.1, R35.2
unnamed: D13.2, R33.1
unnamed: J2.1, Q1.5, Q1.6, Q1.7, Q1.8, Q2.3
unnamed: J10.1, L1.2
unnamed: J11.3, J12.3, J26.1
unnamed: J13.1, JP2.2
unnamed: J28.1, U13.4
unnamed: Q1.4, R1.2, R2.1
unnamed: Q2.1, R3.2, R4.1
unnamed: Q3.3, R35.1
unnamed: R5.1, R7.2, U3.4
unnamed: R19.1, R20.2, U9.2
unnamed: R6.1, R23.2, U4.4
PWR0: J4.7, U8.5
PWR1: J4.10, U8.6
PWR2: J4.9, U8.7
PWR3: J4.12, U8.9
PWR4: J4.11, U8.10
PWR5: J4.14, U8.11
PWR_EN: J4.15, R22.2, R38.2, U8.14
PWR_PG: J4.5, Q3.1, R22.1, U8.4
Trigger: J9.2, J14.1, J16.1
VCC3V3: C39.2, C41.2, C42.2, D12.2, J7.2, J7.4, L4.2, U9.24
VCC5V0: C47.2, C54.1, C55.1, C63.1, J7.5, JP3.3, L5.2, U10.3, U11.3, U13.3
VDDA: C36.2, C37.2, C38.2, C40.2, C45.2, C46.2, R14.1, R15.1, R19.2, U6.5, U9.7, U9.12
VGA_GAIN: J5.3, R13.2
VGA_HILO: J5.1, U7.13
XADCGND: C54.2, C55.2, C63.2, J6.3, J23.2, U10.2, U10.7, U11.2, U11.7, U13.2, U13.7
